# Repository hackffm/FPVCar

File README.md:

# FPVCar
First Person View Car

## Project Page
[FPV_Auto](https://hackerspace-ffm.de/wiki/index.php?title=FPV-Auto) @ HackFFM

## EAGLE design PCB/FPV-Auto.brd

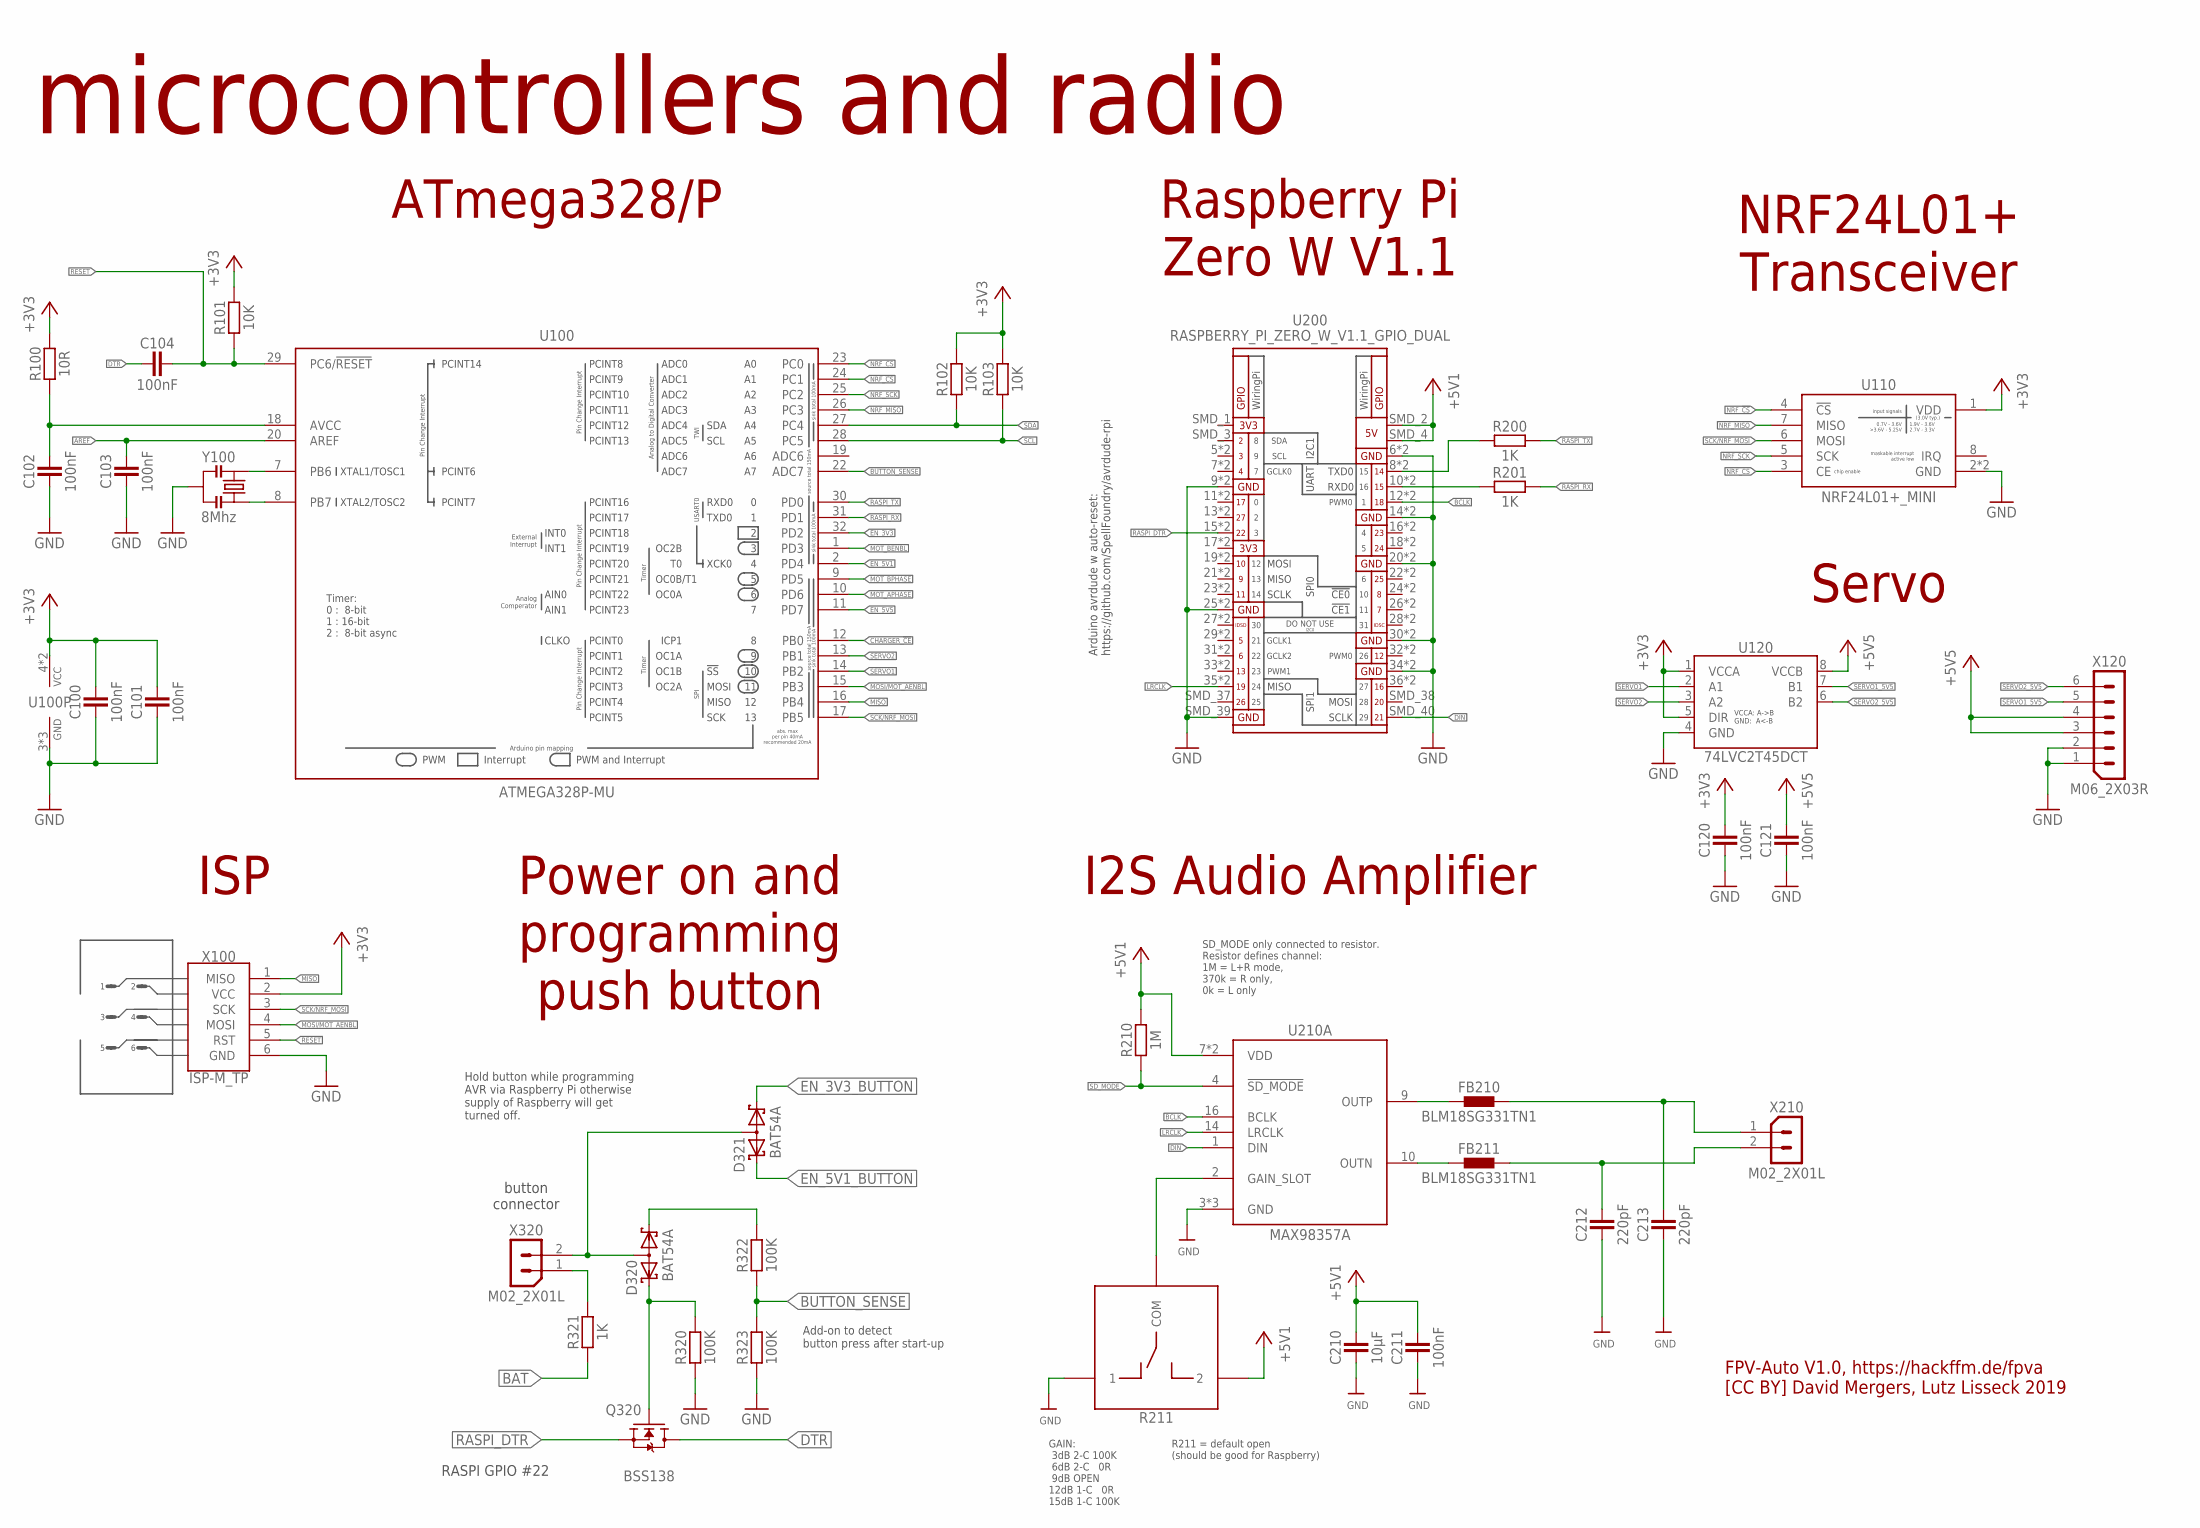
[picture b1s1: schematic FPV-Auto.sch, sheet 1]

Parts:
C100, C101, C102, C103, C104, C120, C121, C211: 100nF; C0603
C210: 10µF; C0603
C212, C213: 220pF; C0603
D320, D321: BAT54A; SOT23
FB210, FB211: BLM18SG331TN1; 0603
Q320: BSS138; SOT23-3
R100: 10R; R0603
R101, R102, R103: 10K; R0603
R200, R201, R321: 1K; R0603
R210: 1M; R0603
R211: R_SWITCH_2_WAY_0603; R0603_SWITCH_2_WAY
R320, R322, R323: 100K; R0603
U100: ATMEGA328P-MU; PBS(S-PQFP-G32)
U110: NRF24L01+_MINI
U120: 74LVC2T45DCT; DCT(R-PDSO-G8)
U200: RASPBERRY_PI_ZERO_W_V1.1_GPIO_DUAL
U210: MAX98357A; 90-0031
X100: ISP-M_TP
X120: M06_2X03R; M2X03R
X210, X320: M02_2X01L; M2X01L
Y100: 8Mhz; CSTNE

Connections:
+3V3: C100.1, C101.1, C120.1, R100.2, R101.2, R102.2, R103.2, U100.4 (VCC), U100.6 (VCC), U110.1 (VDD), U120.1 (VCCA), U120.5 (DIR), X100.2 (VCC); also elsewhere on the board
+5V1: C210.1, C211.1, R210.2, R211.2, U200.SMD_2 (5V), U200.SMD_4 (5V), U210.7 (VDD), U210.8 (VDD); also elsewhere on the board
+5V5: C121.1, U120.8 (VCCB), X120.3, X120.4; also elsewhere on the board
AREF: C103.1, U100.20 (AREF)
BAT: R321.2; also elsewhere on the board
BCLK: U200.12 (GPIO18), U200.SMD_12 (GPIO18), U210.16 (BCLK)
BUTTON_SENSE: R322.1, R323.2, U100.22 (ADC7)
CHARGER_!CE: U100.12 (PB0); also elsewhere on the board
DIN: U200.SMD_40 (GPIO21), U210.1 (DIN)
DTR: C104.2, Q320.3 (D)
EN_3V3: U100.32 (PD2); also elsewhere on the board
EN_3V3_BUTTON: D321.1 (K1); also elsewhere on the board
EN_5V1: U100.2 (PD4); also elsewhere on the board
EN_5V1_BUTTON: D321.2 (K2); also elsewhere on the board
EN_5V5: U100.11 (PD7); also elsewhere on the board
GAIN: R211.COM, U210.2 (GAIN_SLOT)
GND: C100.2, C101.2, C102.2, C103.2, C120.2, C121.2, C210.2, C211.2, C212.2, C213.2, R211.1, R320.1, R323.1, U100.3 (GND), U100.5 (GND), U100.21 (GND), U110.2 (GND), U110.9 (GND), U120.4 (GND), U200.6 (GND), U200.9 (GND), U200.14 (GND), U200.20 (GND), U200.25 (GND), U200.30 (GND), U200.34 (GND), U200.SMD_6 (GND), U200.SMD_9 (GND), U200.SMD_14 (GND), U200.SMD_20 (GND), U200.SMD_25 (GND), U200.SMD_30 (GND), U200.SMD_34 (GND), U200.SMD_39 (GND), U210.3 (GND), U210.11 (GND), U210.15 (GND), U210.TP0 (GND), U210.TP1 (GND), X100.6 (GND), X120.1, X120.2, Y100.2; also elsewhere on the board
LRCLK: U200.35 (GPIO19), U200.SMD_35 (GPIO19), U210.14 (LRCLK)
MISO: U100.16 (PB4), X100.1 (MISO)
MOSI/MOT_AENBL: U100.15 (PB3), X100.4 (MOSI); also elsewhere on the board
MOT_APHASE: U100.10 (PD6); also elsewhere on the board
MOT_BENBL: U100.1 (PD3); also elsewhere on the board
MOT_BPHASE: U100.9 (PD5); also elsewhere on the board
unnamed: D320.3 (AA), D321.3 (AA), X320.2
unnamed: FB211.1, U210.10 (OUTN)
unnamed: FB210.1, U210.9 (OUTP)
unnamed: U100.8 (PB7), Y100.3
unnamed: U100.7 (PB6), Y100.1
unnamed: D320.2 (K2), R322.2
unnamed: D320.1 (K1), Q320.1 (G), R320.2
unnamed: R321.1, X320.1
unnamed: C102.1, R100.1, U100.18 (AVCC)
unnamed: R200.1, U200.8 (GPIO14/TXD0), U200.SMD_8 (GPIO14/TXD0)
unnamed: R201.1, U200.10 (GPIO15/RXD0), U200.SMD_10 (GPIO15/RXD0)
NRF_!CS: U100.24 (PC1), U110.4 (!CS)
NRF_CS: U100.23 (PC0), U110.3 (CE)
NRF_MISO: U100.26 (PC3), U110.7 (MISO)
NRF_SCK: U100.25 (PC2), U110.5 (SCK)
RASPI_DTR: Q320.2 (S), U200.15 (GPIO22/GEN3), U200.SMD_15 (GPIO22/GEN3)
RASPI_RX: R201.2, U100.31 (PD1)
RASPI_TX: R200.2, U100.30 (PD0)
RESET: C104.1, R101.1, U100.29 (PC6/!RESET!), X100.5 (RST)
SCK/NRF_MOSI: U100.17 (PB5), U110.6 (MOSI), X100.3 (SCK)
SCL: R103.1, U100.28 (PC5); also elsewhere on the board
SDA: R102.1, U100.27 (PC4); also elsewhere on the board
SD_MODE: R210.1, U210.4 (!SD_MODE)
SERVO1: U100.14 (PB2), U120.2 (A1)
SERVO1_5V5: U120.7 (B1), X120.5
SERVO2: U100.13 (PB1), U120.3 (A2)
SERVO2_5V5: U120.6 (B2), X120.6
VO+: C213.1, FB210.2, X210.1
VO-: C212.1, FB211.2, X210.2

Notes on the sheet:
microcontrollers and radio
NRF24L01+ Transceiver
Raspberry Pi Zero W V1.1
ATmega328/P
GAIN: 3dB 2-C 100K 6dB 2-C 0R 9dB OPEN 12dB 1-C 0R 15dB 1-C 100K
ISP
I2S Audio Amplifier
Servo
button connector
RASPI GPIO #22
Power on and programming push button
SD_MODE only connected to resistor. Resistor defines channel: 1M = L+R mode, 370k = R only, 0k = L only
R211 = default open (should be good for Raspberry)
Arduino avrdude w auto-reset: https://github.com/SpellFoundry/avrdude-rpi
Hold button while programming AVR via Raspberry Pi otherwise supply of Raspberry will get turned off.
Add-on to detect button press after start-up
FPV-Auto V1.0, https://hackffm.de/fpva [CC BY] David Mergers, Lutz Lisseck 2019

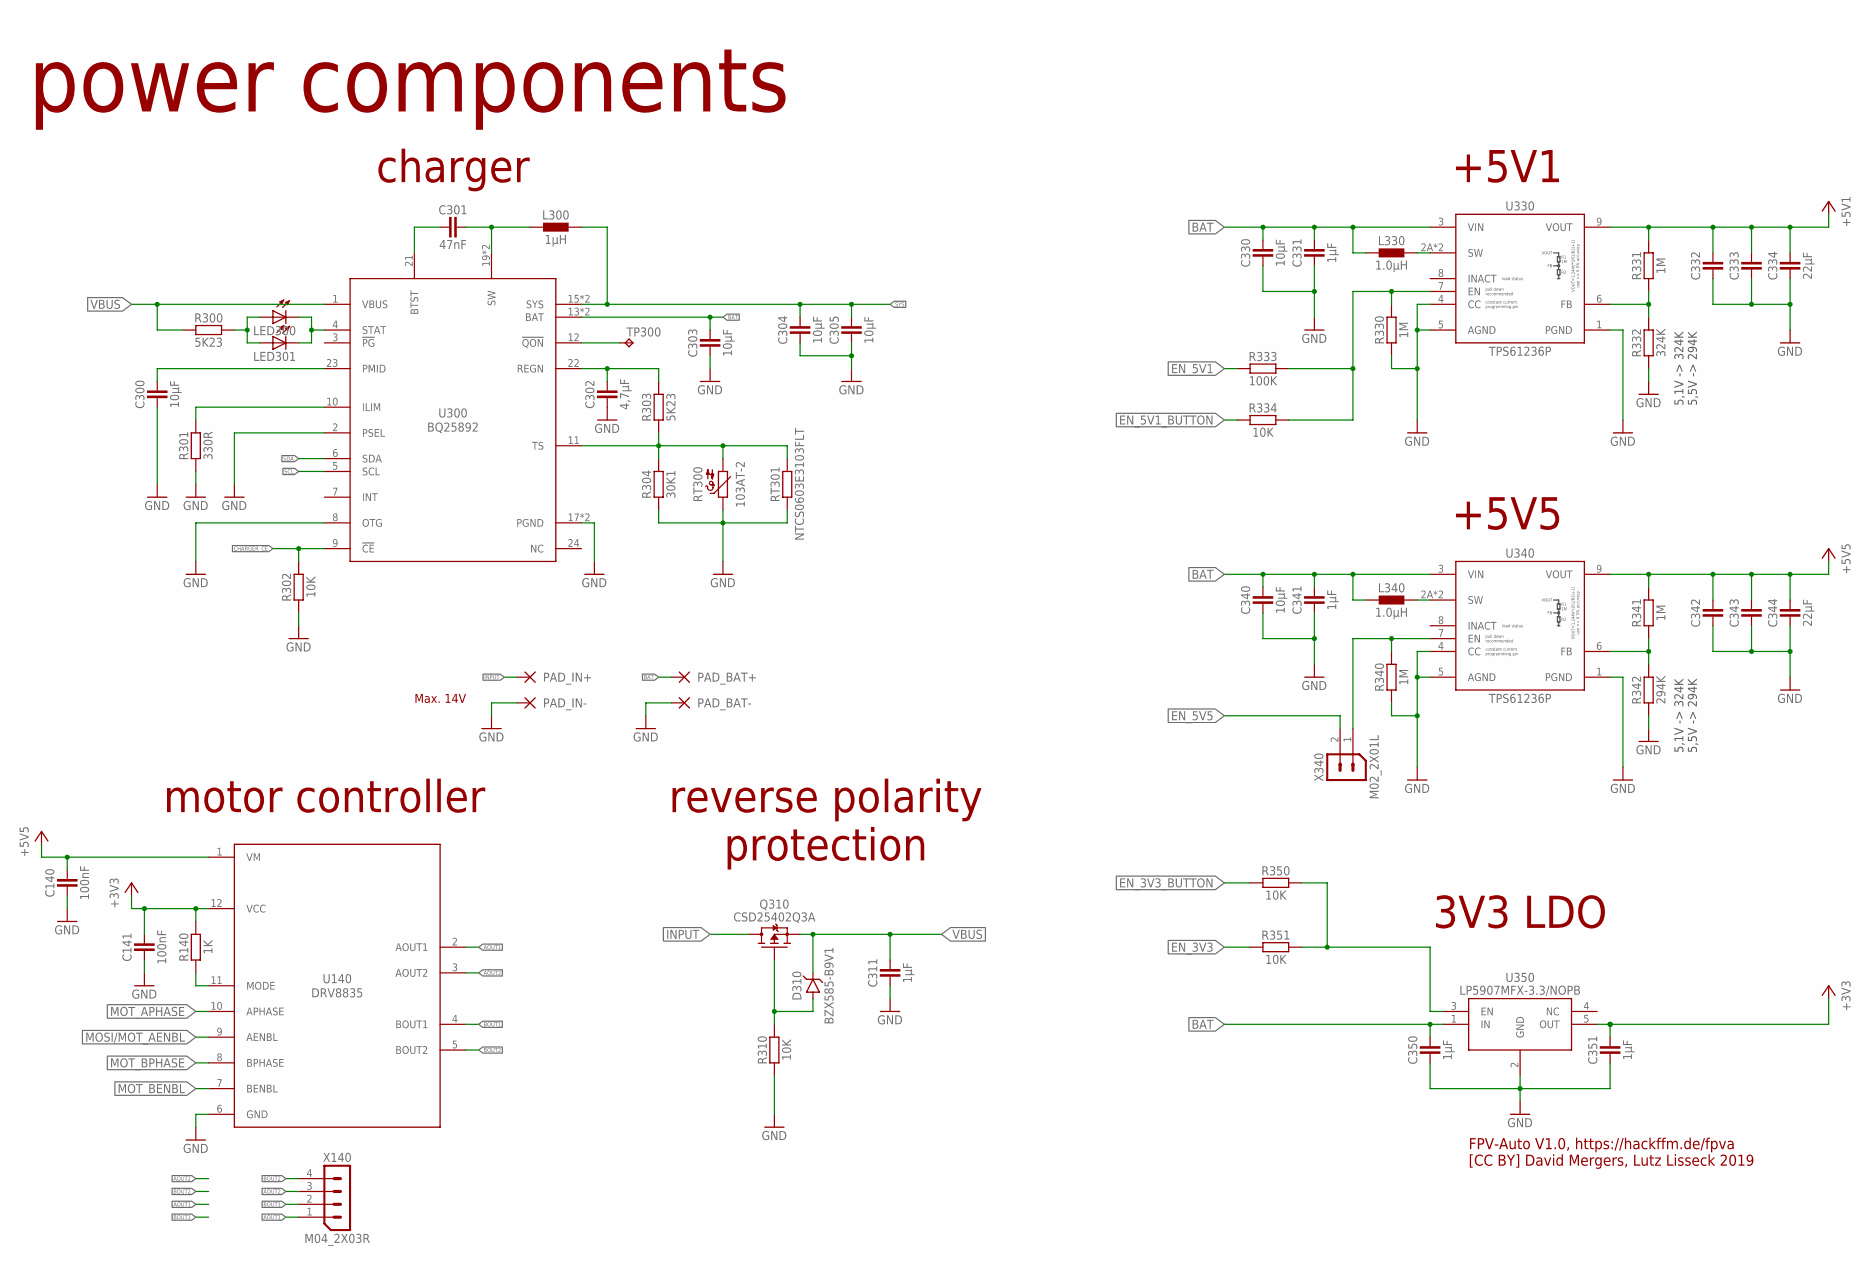
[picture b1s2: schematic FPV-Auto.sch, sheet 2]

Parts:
C140, C141: 100nF; C0603
C300, C303, C304, C305: 10µF; C0805
C301: 47nF; C0402
C302: 4,7µF; C0603
C311: 1µF; C0805
C330, C340: 10µF; C0603
C331, C341, C350, C351: 1µF; C0603
C332, C333, C334, C342, C343, C344: 22µF; C0805
D310: BZX585-B9V1; SOD523(SC-79)
L300: 1µH; 4030
L330, L340: 1.0µH; XAL7030
LED300: LEDCHIP-LED0603; CHIP-LED0603
LED301: LED3MM
PAD_BAT+: WIREPAD2,15/1,0; 2,15/1,0
PAD_BAT-: WIREPAD2,15/1,0; 2,15/1,0
PAD_IN+: WIREPAD2,15/1,0; 2,15/1,0
PAD_IN-: WIREPAD2,15/1,0; 2,15/1,0
Q310: CSD25402Q3A; Q3A
R140: 1K; R0603
R300, R303: 5K23; R0603
R301: 330R; R0603
R302, R310, R334, R350, R351: 10K; R0603
R304: 30K1; R0603
R330, R331, R340, R341: 1M; R0603
R332: 324K; R0603
R333: 100K; R0603
R342: 294K; R0603
RT300: 103AT-2; AT-2
RT301: NTCS0603E3103FLT; R0603
TP300: TPB1,27; B1,27
U140: DRV8835; DSS(WSON-12)
U300: BQ25892; RTW(S-PWQFN-N24)_LONG
U330, U340: TPS61236P; RWL(S-PQFP-N9)_LONG
U350: LP5907MFX-3.3/NOPB; DBV(R-PDSO-G5)
X140: M04_2X03R; M2X02R
X340: M02_2X01L; M2X01L

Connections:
+3V3: C141.1, C351.1, R140.1, U140.12 (VCC), U350.5 (OUT); also elsewhere on the board
+5V1: C332.1, C333.1, C334.1, R331.2, U330.9 (VOUT); also elsewhere on the board
+5V5: C140.1, C342.1, C343.1, C344.1, R341.2, U140.1 (VM), U340.9 (VOUT); also elsewhere on the board
AOUT1: U140.2 (AOUT1), X140.1
AOUT2: U140.3 (AOUT2), X140.3
BAT: C303.1, C330.1, C331.1, C340.1, C341.1, C350.1, L330.1, L340.1, PAD_BAT+.1, U300.13 (BAT), U300.14 (BAT), U330.3 (VIN), U340.3 (VIN), U350.1 (IN); also elsewhere on the board
BOUT1: U140.4 (BOUT1), X140.2
BOUT2: U140.5 (BOUT2), X140.4
CHARGER_!CE: R302.2, U300.9 (!CE); also elsewhere on the board
EN_3V3: R351.1; also elsewhere on the board
EN_3V3_BUTTON: R350.1; also elsewhere on the board
EN_3V3_JMP: R350.2, R351.2, U350.3 (EN)
EN_5V1: R333.1; also elsewhere on the board
EN_5V1_BUTTON: R334.1; also elsewhere on the board
EN_5V1_JMP: R330.2, R333.2, R334.2, U330.7 (EN)
EN_5V5: X340.2; also elsewhere on the board
EN_5V5_JMP: R340.2, U340.7 (EN), X340.1
GND: C140.2, C141.2, C300.2, C302.2, C303.2, C304.2, C305.2, C311.2, C330.2, C331.2, C332.2, C333.2, C334.2, C340.2, C341.2, C342.2, C343.2, C344.2, C350.2, C351.2, PAD_BAT-.1, PAD_IN-.1, R301.1, R302.1, R304.1, R310.1, R330.1, R332.1, R340.1, R342.1, RT300.P$1 (1), RT301.1, U140.6 (GND), U140.TP (GND), U140.TP1 (GND), U140.TP2 (GND), U140.TP3 (GND), U300.2 (PSEL), U300.8 (OTG), U300.17 (PGND), U300.18 (PGND), U300.TP0 (GND), U300.TP1 (GND), U300.TP2 (GND), U300.TP3 (GND), U300.TP4 (GND), U300.TP5 (GND), U300.TP6 (GND), U300.TP7 (GND), U300.TP8 (GND), U300.TP9 (GND), U330.1 (PGND), U330.4 (CC), U330.5 (AGND), U340.1 (PGND), U340.4 (CC), U340.5 (AGND), U350.2 (GND); also elsewhere on the board
INPUT: PAD_IN+.1, Q310.1 (D), Q310.2 (D), Q310.3 (D)
MOSI/MOT_AENBL: U140.9 (AENBL); also elsewhere on the board
MOT_APHASE: U140.10 (APHASE); also elsewhere on the board
MOT_BENBL: U140.7 (BENBL); also elsewhere on the board
MOT_BPHASE: U140.8 (BPHASE); also elsewhere on the board
unnamed: L330.2, U330.2A (SW), U330.2B (SW)
unnamed: L340.2, U340.2A (SW), U340.2B (SW)
unnamed: R341.1, R342.2, U340.6 (FB)
unnamed: R331.1, R332.2, U330.6 (FB)
unnamed: TP300.TP, U300.12 (!QON)
unnamed: R303.1, R304.2, RT300.P$2 (2), RT301.2, U300.11 (TS)
unnamed: C302.1, R303.2, U300.22 (REGN)
unnamed: R301.2, U300.10 (ILIM)
unnamed: C301.2, U300.21 (BTST)
unnamed: C301.1, L300.P$1 (1), U300.19 (SW), U300.20 (SW)
unnamed: D310.A, Q310.4 (G), R310.2
unnamed: C300.1, U300.23 (PMID)
unnamed: LED300.C, LED301.K (C), U300.4 (STAT)
unnamed: LED300.A, LED301.A, R300.1
unnamed: R140.2, U140.11 (MODE)
SCL: U300.5 (SCL); also elsewhere on the board
SDA: U300.6 (SDA); also elsewhere on the board
SYS: C304.1, C305.1, L300.P$2 (2), U300.15 (SYS), U300.16 (SYS)
VBUS: C311.1, D310.C, Q310.TP0 (S), Q310.TP1 (S), Q310.TP2 (S), Q310.TP3 (S), Q310.TP4 (S), Q310.TP5 (S), Q310.TP6 (S), Q310.TP7 (S), R300.2, U300.1 (VBUS)

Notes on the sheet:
power components
+5V1
motor controller
3V3 LDO
5,1V -> 324K 5,5V -> 294K
+5V5
charger
reverse polarity protection
Max. 14V
FPV-Auto V1.0, https://hackffm.de/fpva [CC BY] David Mergers, Lutz Lisseck 2019

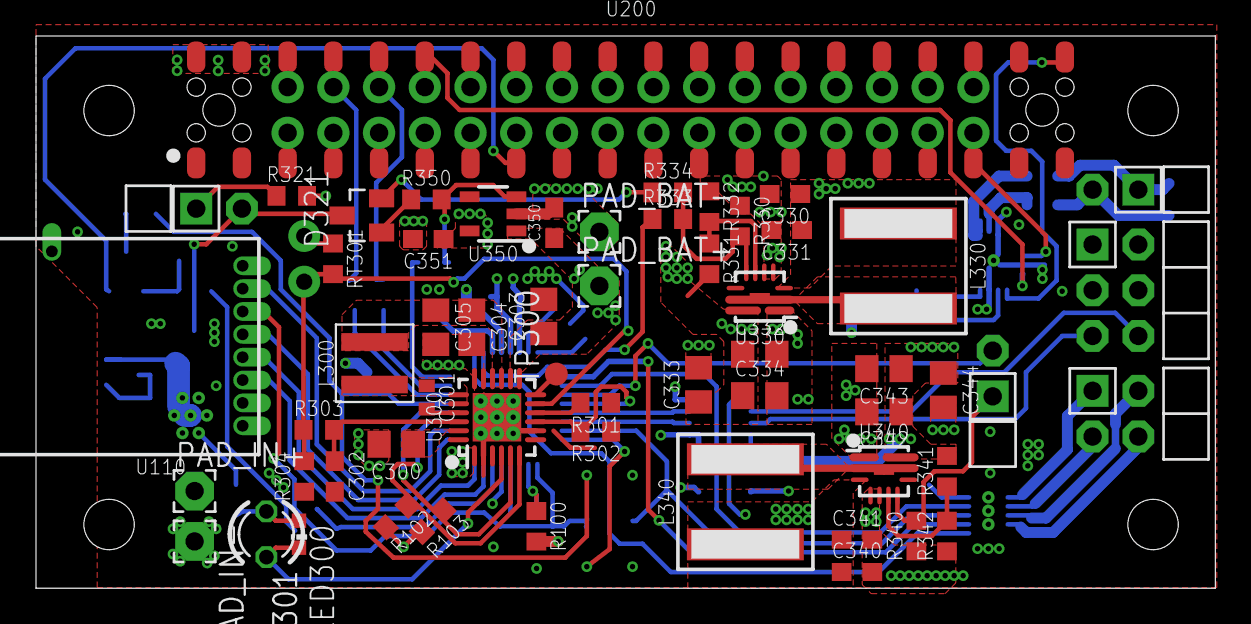
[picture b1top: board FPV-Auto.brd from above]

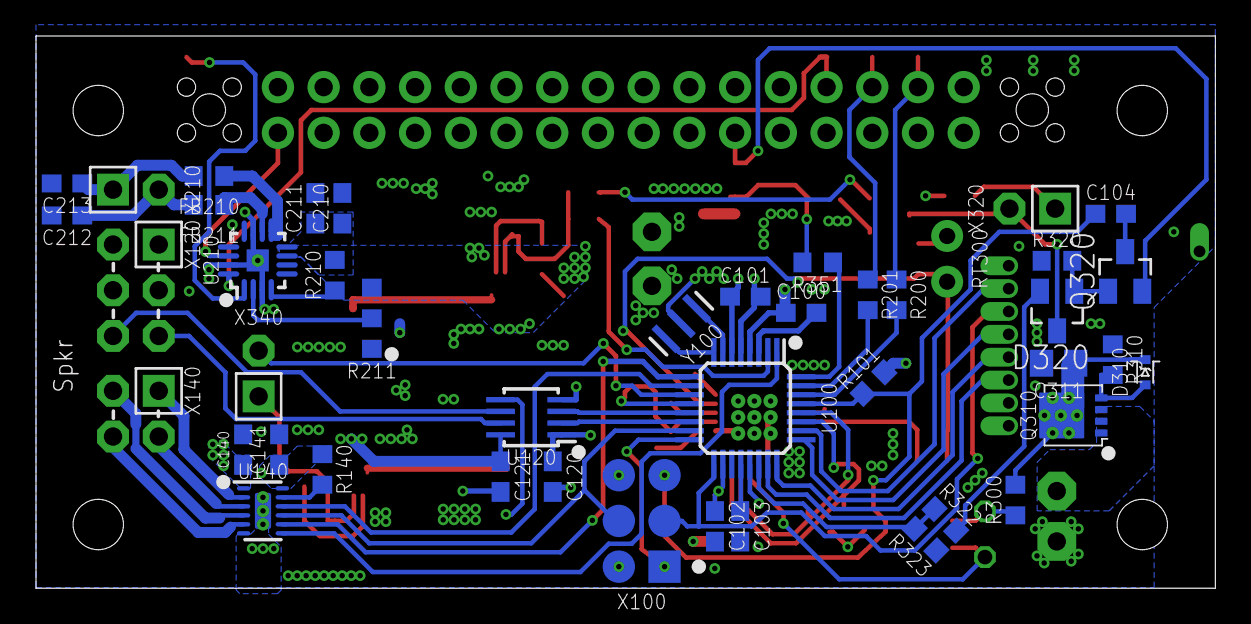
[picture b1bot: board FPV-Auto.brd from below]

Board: 4 copper layers, 65.5 x 30.7 mm, 99 parts (40 on the bottom side), 77 nets.

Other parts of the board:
U$3: HACKFFM_LOGO_STOP
U$9: DATE

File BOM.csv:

Qty;Value;Device;Package;Parts;OC_MOUSER
;;LED3MM;LED3MM;LED301;
1;;LEDCHIP-LED0603;CHIP-LED0603;LED300;720-LSL29K-G1J2-1-Z
1;;R;R0603;RT301;594-NTCS0603E3103FLT
2;1.0µH;XAL7030-102ME;XAL7030;L330, L340;994-XAL7030-102ME
4;100K;R;R0603;R320, R322, R323, R333;603-RT0603FRE07100KL
10;100nF;C0603;C0603;C100, C101, C102, C103, C104, C120, C121, C140, C141, C211;80-C0603C104M5RAUTO
;103AT-2;103AT-2;AT-2;RT300;
8;10K;R;R0603;R101, R102, R103, R302, R310, R334, R350, R351;603-RT0603FRE0710KL
1;10R;R;R0603;R100;603-RT0603FRE0710RL 
3;10µF;C0603;C0603;C210, C330, C340;81-GRM188R61A106KE9J
4;10µF;C0805;C0805;C300, C303, C304, C305;81-GRJ21BR61E106KE1K
4;1K;R;R0603;R140, R200, R201, R321;603-RT0603FRE071KL
5;1M;R;R0603;R210, R330, R331, R340, R341;603-RC0603FR-071ML
4;1µF;C0603;C0603;C331, C341, C350, C351;810-CGA3E1X7R1V105KA
1;1µF;C0805;C0805;C306;603-CC805KKX7R9BB105
1;1µH;78438357010;4030;L300;710-78438357010 
2;220pF;C0603;C0603;C212, C213;80-C0603C221JDGAUTO
6;22µF;C0805;C0805;C332, C333, C334, C342, C343, C344;81-GRM219R61C226ME1K
1;294K;R;R0603;R342;603-RT0603DRE07294KL
1;30K1;R;R0603;R304;603-RT0603FRE0730K1L 
1;324K;R;R0603;R332;603-RT0603FRE07324KL
1;4,7µF;C0603;C0603;C302;81-GRT188C81E475KE3D
1;47nF;C0402;C0402;C301;810-A2B1X8473K5BE
2;5K23;R;R0603;R300, R303;603-RT0603FRE075K23L
1;74LVC2T45DCT;74LVC2T45DCT;DCT(R-PDSO-G8);U120;595-SN74LVC2T45DCTR
1;8Mhz;CSTNE8M00GH5C000R0;CSTNE;Y100;81-CSTNE8M00GH5C000R
1;?;R;R0603;R301;
1;ATMEGA328P-AU;ATMEGA328P-AU;PBS(S-PQFP-G32);U100;556-ATMEGA328P-AU
2;BAT54A;BAT54A;SOT23;D320, D321;755-BAT54AHMFHT116
2;BLM18SG331TN1;BLM18SG331TN1;603;FB210, FB211;
1;BQ25892;BQ25892;RTW(S-PWQFN-N24)_LONG;U300;595-BQ25892RTWR
1;BSS138;BSS138;SOT23-3;Q320;512-BSS138
1;BZX585-B9V1;BZX585-B9V1;SOD523(SC-79);D310;771-BZX585-B9V1115
1;CSD25402Q3A;CSD25402Q3A;Q3A;Q310;595-CSD25402Q3A
1;DRV8835;DRV8835;DSS(WSON-12);U140;595-DRV8835DSSR
1;LP5907MFX-3.3/NOPB;LP5907MFX-3.3/NOPB;DBV(R-PDSO-G5);U350;595-LP5907MFX-3.3NPB
3;M02_2X01L;M02_2X01L;M2X01L;X210, X320, X340;
1;M04_2X03R;M04_2X03R;M2X02R;X140;
1;M06_2X03R;M06_2X03R;M2X03R;X120;
1;MAX98357A;MAX98357A;90-0031;U210;700-MAX98357AETE+T
1;NRF24L01+_MINI;NRF24L01+_MINI;NRF24L01+_MINI;U110;
1;RASPBERRY_PI_ZERO_W_V1.1_GPIO_DUAL;RASPBERRY_PI_ZERO_W_V1.1_GPIO_DUAL;RASPBERRY_PI_ZERO_W_V1.1_GPIO_DUAL;U200;
1;R_SWITCH_2_WAY_0603;R_SWITCH_2_WAY_0603;R0603_SWITCH_2_WAY;R211;
2;TPS61236P;TPS61236P;RWL(S-PQFP-N9)_LONG;U330, U340;595-TPS61236PRWLR
;;;;;
1;;;;XU200;855-M20-7812045

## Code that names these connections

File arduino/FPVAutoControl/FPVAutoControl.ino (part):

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#define POWERHOLD 2
#define MOTOR_SLEEP 7

#define EN_3V3         2
#define EN_5V1         4
#define EN_5V5         7
#define CHARGER_CE     8
#define DRV_AENBL     11
#define DRV_BENBL      3
#define DRV_APHASE     6
#define DRV_BPHASE     5
#define BUTTON_SENSE  A7

#define CHARGER_ADR   0x6B

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  Serial.begin(38400);
  Wire.begin();
  
  pinMode(EN_3V3, OUTPUT);
  digitalWrite(EN_3V3, HIGH); 
  
  pinMode(EN_5V1, OUTPUT);
  digitalWrite(EN_5V1, HIGH);  
  
  pinMode(DRV_AENBL, OUTPUT); 
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  myservo2.write(90);  
  delay(100);
  
  pinMode(EN_5V5, OUTPUT);
  digitalWrite(EN_5V5, HIGH);

  
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
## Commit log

2018-08-15 Serial command dispatcher and motor driver
2018-08-16 added webserver from the spacerex project
2018-08-20 changed driving the DRV8833 from two PWMs to one PWM for one tire pair
2018-09-03 README.md update
2018-09-04 added: 3d-parts
2019-02-27 added: PCB-Layout
2019-03-01 Changes on Raspberry GPIO assignment
2019-03-02 Update PCB Layout
2019-03-03 Z-Diode on reverse-prot-mosfet, button also on AVR, other minor changes
2019-03-04 updated lib and pcb
2019-03-04 Kommentare...
2019-03-05 Updated PCB
2019-03-11 Add BOM
2019-03-15 Board Layout Update
    changed mask, changed 0402 caps -> 0603
2019-03-16 Silkscreen and Schematic Docu updates
2019-03-17 Schematic PDF added
2019-03-17 Updated BOM
2019-03-18 Add block diagram
2019-04-18 pcb-update
2019-04-25 Arduino hardware folder for easy use added
2019-04-25 Made bin files executable
2019-04-25 First version of control software
2019-04-29 Motor and Servo works now
2019-05-06 I2C commands added for charger communication
2019-05-15 pygame added usw
2019-05-21 hostname for stream and websocket is now dynamic set by tornado via a template mechanism
2019-05-22 modified app2.py and renamed it to server_p3.py that it runs under python3
2019-05-22 add chicken sound, played with pygame
2019-05-26 facial expressions for oled i2c display with 128x64
2019-05-29 fixed bug with arvdude and path
2019-06-04 fixed the serial channel to the website. was broken when we changed to python3
2019-06-04 add V for reading the bus voltage(input voltage)
2019-06-06 the chuncks of serial data from arduino are consolidated to commands within the python webserver. vbat and vbus are displayed on the webinterface
2019-06-07 add gitignorefile
2019-06-07 removed old webserver scripts for python2
2019-06-18 flask tests
2019-06-18 add hello world flask
2019-06-18 flask demo with templates and static content
2019-06-18 flask example with websocket
2019-06-21 neues Beispiel für Webfrontend
2019-06-24 removanle controls for FPV experience
2019-07-01 flask example extended for serial connection and echo from web page
2019-07-02 webserver moved to flask to 90%
2019-07-05 change 03 to bootstrap
2019-07-07 add gamepad controler
2019-07-08 removed gamepad and finished boostrap for 03
2019-07-14 add base class module
2019-07-14 cleanup
2019-07-15 rename module to component
2019-07-15 component dictionary
2019-07-17 renamed robota to fpvc. moved console output to handler.some tweaks for the class approach
2019-07-17 remove unwanted files. commit missed commits
2019-07-17 cleanup, renaming functions to make more sense
2019-07-18 add comments to not accidentialy delete stuff
2019-07-18 working sound component added
2019-07-18 Base component sends move command to serial now
2019-07-19 renamed module to component
2019-07-20 made more pep8 compliant
2019-07-22 create default handler and rely on it
2019-07-22 remove extra message section in request
2019-07-22 remove is_type as not relevant anymore
2019-07-22 port change to 9090
2019-07-22 Lutzkram
2019-07-22 nonsense
2019-07-22 switched back from flask to tornado because of massive performance problems with socketio
2019-07-22 server works now
2019-07-29 create flask 03_web_console in tornado folder
2019-07-30 use icon for toggling controls
2019-07-30 change clickable button to div
2019-07-30 change web name to first person view car
2019-07-31 change bootstrap to be local installed
2019-08-01 css changes to align elements in canvas joystick
2019-08-02 minor tweaks on the ui
2019-08-03 Added part mounting plan
2019-08-03 Fixes for bootloading and mega328p
2019-08-07 moved the components into the module components and splitted them into individual files
2019-08-14 the mjpg-streamer can get startet from the web site
2019-09-16 service unit and mjpg-streamer is local now
2019-09-30 cam resolution and quality
2019-10-07 bq25892 stats
2019-10-19 start working on bno055
2019-10-19 basic test for bno055
2019-10-19 first version for bno055 component
2019-10-20 add option for all sensor values at once
2019-10-20 align with origin
2019-10-20 add logs folder
2019-10-20 add netiface lib to requierements
2019-10-20 move helper functions to component
2019-10-20 add serial
2019-10-20 start minimal working web example
2019-10-20 change back wrongly edited file
2019-10-20 add debug option to 04 stats component
2019-10-20 lost concentration...
2019-10-20 website for bno055
2019-10-20 rework to handle return value from components. not working nicely now
2019-10-21 change to new message format
2019-10-21 better output
2019-10-21 works, but unclear why sensor values only updated in tests cases
2019-10-21 always return a dict from bno055 component
2019-10-25 start finding how to use bno055 without static loading
2019-10-25 make test more human readable
2019-10-26 additional infos in print
2019-10-27 add calibration status
2019-10-29 update canvasJoystick with PS3 controller support
2019-11-04 328p added in Arduino Raspberry Boards
2019-11-05 add canvasCompass again
2019-11-11 add test for serial connection
2019-11-11 add wait cycle
2019-11-11 shorter wait cycle
2019-11-11 restructure async routines
2019-11-17 incorporate all minore poc's
2019-11-18 enabled gauges and shutdown button
2019-11-18 pcb partlist doku
2019-11-25 fpv web ui. mostly clean v1. Gauges can't be hidden currently
2019-11-26 some js linting and checking for good postion
2019-11-26 take over some linting and checking
2019-11-26 cleanup rect
2019-11-28 reducing adafruit webgl demo to a simple server side event page
2019-11-30 rename file to make clear it's bash
2019-11-30 transfere sse example to component with websocket
2019-11-30 align webserver of 03 and 04
2019-11-30 backport bno055 from 04 to 03
2019-11-30 align fpvcar.js of 03 and 04
2019-11-30 transfere ui experiments to 03. Remove dedicated js for bno055
2019-12-02 backport prod components
2019-12-02 remove double component is valid check. Get some missing stuff from backports
2019-12-02 remove unused functions. Handle odd websocket calls
2019-12-02 video in ui example
2019-12-02 video files
2019-12-03 untested config handler
2019-12-04 backport to ui test.Still untested
2019-12-04 more confident with config. still untested
2019-12-05 Update requierements.txt
    add paygame
2019-12-06 remove video tag
2019-12-09 add tests and config resource
2019-12-09 start working with config component in front and backend. Also tests
2019-12-10 config offers now a cfg.keyname access for config values
2019-12-10 reduce global variables
2019-12-10 handle bno055 more component align
2019-12-10 use configurable debug better
2019-12-11 add get and set to component_config for values. stores instantly to file
2019-12-11 start sensors(bno055) to be configurable if present
2019-12-12 realise that real json has to be used in config.json
2019-12-12 better socket handling. add test_component_base to start base handling
2019-12-12 more self explaining. remove depricated js stuff
2019-12-13 nothing really
2019-12-13 adding debug to config page. Not functional !
2019-12-14 enable config load from config.json during page load
2019-12-14 Update bno055.py
    remove noisy debug message from sensor
2019-12-14 add bno055 and port to config page
2019-12-15 enable shutdown with os shutdown
2019-12-15 sounds are now a dynamic list from sounds folder
2019-12-16 alphabthical order, item postioning
2019-12-16 use only textarea OutputMessage as debug window
2019-12-16 start optimising shutdown process
2019-12-17 handle different sound lengths
2019-12-18 start working on manage sounds page
2019-12-18 add stuff which could be missing to setup
2019-12-18 continued a bit manage sounds
2019-12-19 upload and delete finished
2019-12-22 styles added
2019-12-24 rename requirements
2019-12-27 add basic camera test
2019-12-28 fix typo in setup
2019-12-28 make serial port configurable
2019-12-30 orientation test
2019-12-30 max size for video
2019-12-30 start intigrating background video
2019-12-30 mjpeg-streamer missing so files added
2019-12-30 page reload when camera starts or stops
2019-12-30 100 procent video background
2019-12-30 vertical canvas distortion removed
2020-01-01 backport changes form orientation tree
2020-01-03 nothin really
2020-01-20 new frontend works now with self scaling touch area
2020-01-25 bidirectional ws communication between two tornado servers
2020-01-27 labyrinth
2020-01-27 player site with ws connection
2020-01-28 player view shows stream
2020-01-28 connect to labyrinth
2020-01-28 car connects to labyrinth
2020-01-28 labyrint sends received message to all connected ws clients
2020-01-30 add canvas joystick to player page
2020-01-31 reduce canvasjoystick to a needed minimum
2020-02-01 centered square
2020-02-02 config with TOML and player dispatcher
2020-02-02 player infos as first message
2020-02-03 communication stuff'
2020-02-03 add missing js file
2020-02-07 Joystick not working
2020-02-09 start experimenting with serial adpater component
2020-02-09 Adapter_Devices(DevicesList) <= Device(name,SerialPort)
2020-02-09 add test page server
2020-02-10 modules
2020-02-11 The things concept partially implemeted
2020-02-11 find and connect attached serial devices
2020-02-12 start working on things page
2020-02-12 slight bug fixes
2020-02-13 logic of add/remove keycard via rfid works
2020-02-13 add some files again
2020-02-14 Things Test
2020-02-16 Serial Thing Name on page. Send text command through websocket
2020-02-17 Serial prototype and logic name space
2020-02-17 ps3 tests
2020-02-18 start backporting and working serial_handler
2020-02-19 start testing serial_handler
2020-02-20 typo
2020-02-20 refresh config.py for every test run
2020-02-21 talk to and find thingies not things
2020-02-22 thing_serial.py verfication. talking to thingies after verification
2020-02-23 failed testing
2020-02-23 remove verification enforcement
2020-02-23 add physical test for labyrinth things
2020-02-24 some ps3 controller tests
2020-02-25 SerialHandler works now in duplex mode
2020-03-02 ignore vs code config
2020-03-05 new protocol between the labyrinth and the mcu's
2020-05-04 IRDA added
2020-05-19 More work on AVR and M0 control MCUs
2020-05-23 First complete IRDA code (untested)
2020-05-25 Long button press detect
2020-05-25 bugfix
2020-05-25 Fixed TXEN
2020-05-28 Minor stuff
2020-06-01 Minor IRDA Adjustments
2020-06-22 complex communication structure implemented
2020-06-22 wrong ident fix
2020-06-30 'documentation'
2020-07-06 something
2020-07-06 steering works somehow now
2020-07-13 camer rotated
2020-07-13 joystick
2020-07-13 white light serverside
2020-07-13 white light in car
2020-07-13 servos car side
2020-07-13 servos server side
2020-07-20 uv led and switch off
2020-07-27 Colopicker
2020-07-27 color led
2020-08-03 ir codes labyrinth
2020-08-03 ir codes car
2020-09-07 forgotten
2020-09-07 'something'
2020-09-07 'ir'
2020-09-21 config stuff
2020-10-05 'someting'
2020-10-05 logo added
2020-10-05 ascii logo
2020-10-05 serial connection to fpvcar got its own class
2020-10-05 simplyfied serial
2020-10-19 more logging
2023-05-01 Bump flask from 1.0.3 to 2.3.2 in /python/flask/03_web_control
    Bumps [flask](https://github.com/pallets/flask) from 1.0.3 to 2.3.2.
    - [Release notes](https://github.com/pallets/flask/releases)
    - [Changelog](https://github.com/pallets/flask/blob/main/CHANGES.rst)
    - [Commits](https://github.com/pallets/flask/compare/1.0.3...2.3.2)
    ---
    updated-dependencies:
2023-05-25 Bump tornado from 6.0.2 to 6.3.2
    Bumps [tornado](https://github.com/tornadoweb/tornado) from 6.0.2 to 6.3.2.
    - [Changelog](https://github.com/tornadoweb/tornado/blob/master/docs/releases.rst)
    - [Commits](https://github.com/tornadoweb/tornado/compare/v6.0.2...v6.3.2)
    ---
    updated-dependencies:
    - dependency-name: tornado
2023-08-22 Add renovate.json

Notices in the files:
parts and their libraries:
microbuilder: This work is placed in the public domain, and may be freely used for commercial and non-commercial work with the following conditions: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
